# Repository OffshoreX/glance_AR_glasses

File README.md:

# GLANCE: Autofocal Reading Glasses (Board 2)

GLANCE started as AR smart glasses and became a sensing platform for **autofocal reading glasses**. An outward-facing distance sensor measures how far away the object in front of you is. Two inward-facing infrared eye sensors estimate where your eyes are pointing. Together they estimate the distance you are actually looking at, which is the signal a focus-tunable lens would need to adjust itself. The lens itself is out of scope for this project. This repo covers the electronics that do the sensing.

**Status:** PCB design is complete and passes design rule checks. Boards are being ordered for the Hack Club Half Life program. Nothing here has been fabricated or tested yet, so no measured results are claimed.

## How it works

- **Brain:** ESP32-S3-WROOM-1 module (Wi-Fi, BLE and native USB). The antenna end overhangs the board edge.
- **Eye sensing:** one 940 nm IR LED (IR333-A) and one phototransistor (PT334-6B) per eye, on an off-board eye module. Four phototransistor channels are read by an ADS1115 16-bit I2C ADC.
- **Distance sensing:** header for an outward-facing time-of-flight distance sensor module.
- **Power:** USB-C input, MCP73831 Li-ion charger, JST PH battery connector, slide switch for power, AP2112K-3.3 LDO for the 3.3 V rail.
- **Input:** four tactile buttons.

## Images

**Schematic:**

**Before placing and routing:**

**After:**

## Board

- 2-layer FR-4, 37.75 x 65 mm
- Power nets on wider tracks, solid GND pour on both layers
- USB D+ and D- routed by hand as a pair. The remaining signals were autorouted with Freerouting (score 990/1000, 31 vias), then cleaned up by hand
- DRC: zero real errors at submission

## Repo layout

```
hardware/
  board2/                KiCad 10 project (glance-board2.*)
  gerbers/               Gerber and drill files for JLCPCB
  images/                README images
  glance_pcb_bom.csv     Full bill of materials with LCSC part numbers
firmware/                Firmware (ESP32-C3 code from the earlier Board 1 design)
```

Board 1 (the original ESP32-C3 AR design) is kept in the repo for history and is not part of this submission.

## Bill of materials

The full BOM with LCSC part numbers and prices is in [`hardware/glance_pcb_bom.csv`](hardware/glance_pcb_bom.csv). Parts come from LCSC and the bare PCBs from JLCPCB. Several LCSC parts have minimum orders of 5 or 10, so more parts are ordered than the board uses.

Funding note: the Half Life BOM table lists only the items covered by the $30 Tier 1 grant. The remaining parts (ADS1115, charger, LDO, connectors, switches, phototransistors) are bought in the same order and paid for personally. The ESP32-S3 module is also self-funded.

## Firmware

Board 2 firmware has not been written yet. The existing code in `firmware/` targets Board 1's ESP32-C3.

## Next steps

1. Receive the boards and check continuity with a multimeter before powering up.
2. Solder, then bring up power, USB and the ADC.
3. Read the eye sensors and the distance sensor, then estimate gaze distance.

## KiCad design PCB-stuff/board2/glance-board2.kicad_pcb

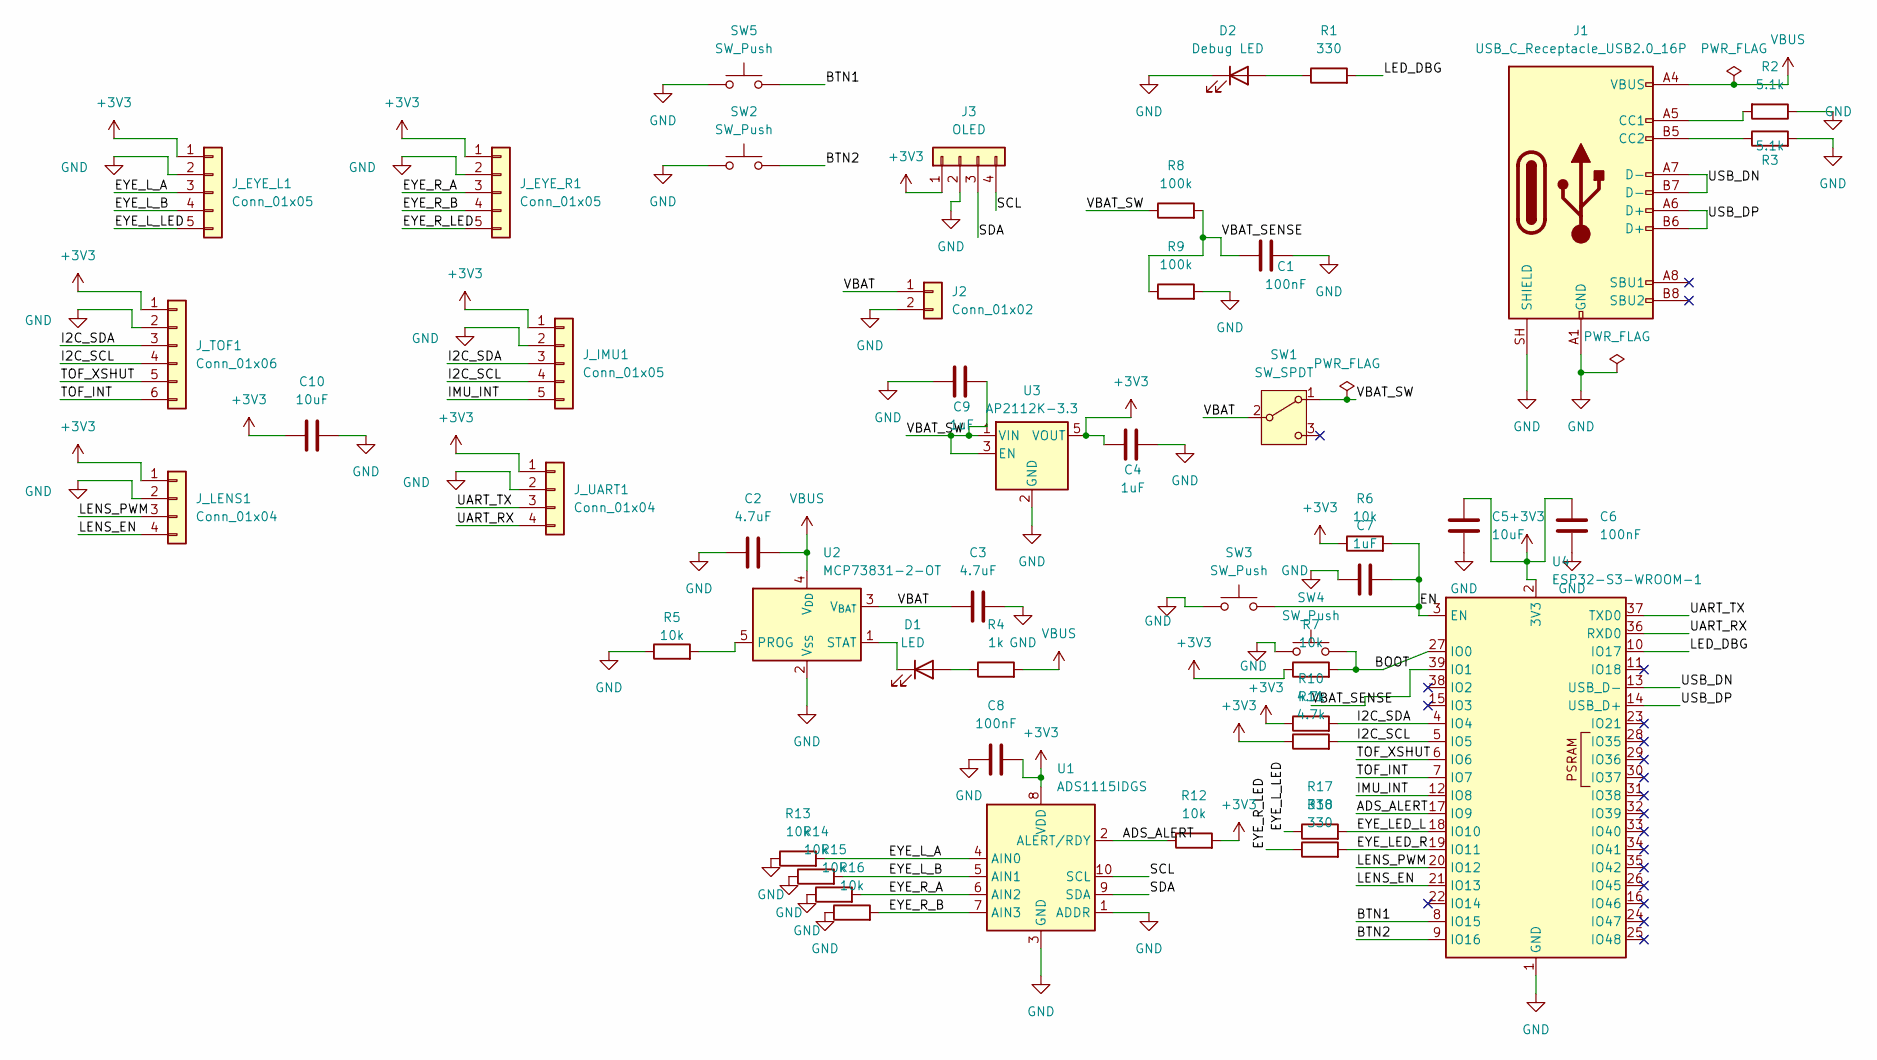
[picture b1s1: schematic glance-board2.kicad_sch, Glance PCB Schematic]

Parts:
C1, C6, C8: 100nF; C_0603_1608Metric
C2, C3: 4.7uF; C_0603_1608Metric
C4, C7, C9: 1uF; C_0603_1608Metric
C5, C10: 10uF; C_0603_1608Metric
D1: LED; LED_0603_1608Metric
D2: Debug LED; LED_0603_1608Metric
J1: USB_C_Receptacle_USB2.0_16P; USB_C_Receptacle_HRO_TYPE-C-31-M-12
J2: Conn_01x02; JST_PH_S2B-PH-K_1x02_P2.00mm_Horizontal
J3: OLED; PinHeader_1x04_P2.54mm_Vertical
J_EYE_L1: Conn_01x05; PinSocket_1x05_P2.54mm_Vertical
J_EYE_R1: Conn_01x05; PinSocket_1x05_P2.54mm_Vertical
J_IMU1: Conn_01x05; PinSocket_1x05_P2.54mm_Vertical
J_LENS1: Conn_01x04; PinSocket_1x04_P2.54mm_Vertical
J_TOF1: Conn_01x06; PinSocket_1x06_P2.54mm_Vertical
J_UART1: Conn_01x04; PinSocket_1x04_P2.54mm_Vertical
R1, R17, R18: 330; R_0603_1608Metric
R2, R3: 5.1k; R_0603_1608Metric
R4: 1k; R_0603_1608Metric
R5, R6, R7, R12, R13, R14, R15, R16: 10k; R_0603_1608Metric
R8, R9: 100k; R_0603_1608Metric
R10, R11: 4.7k; R_0603_1608Metric
SW1: SW_SPDT; SW_SPDT_PCM12
SW2, SW3, SW4, SW5: SW_Push; SW_SPST_B3U-1000P
U1: ADS1115IDGS; TSSOP-10_3x3mm_P0.5mm
U2: MCP73831-2-OT; SOT-23-5
U3: AP2112K-3.3; SOT-23-5
U4: ESP32-S3-WROOM-1

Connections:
+3V3: C4.1, C5.1, C6.1, C8.2, C10.1, J3.1, J_EYE_L1.1, J_EYE_R1.1, J_IMU1.1, J_LENS1.1, J_TOF1.1, J_UART1.1, R6.1, R7.1, R10.1, R11.1, R12.2, U1.8 (VDD), U3.5 (VOUT), U4.2 (3V3)
/ADS_ALERT: R12.1, U1.2 (ALERT/RDY), U4.17 (IO9)
/BOOT: R7.2, SW4.2, U4.27 (IO0)
/BTN1: SW5.2, U4.8 (IO15)
/BTN2: SW2.2, U4.9 (IO16)
/EN: C7.2, R6.2, SW3.2, U4.3 (EN)
/EYE_LED_L: R17.2, U4.18 (IO10)
/EYE_LED_R: R18.2, U4.19 (IO11)
/EYE_L_A: J_EYE_L1.3, R13.2, U1.4 (AIN0)
/EYE_L_B: J_EYE_L1.4, R14.2, U1.5 (AIN1)
/EYE_L_LED: J_EYE_L1.5, R17.1
/EYE_R_A: J_EYE_R1.3, R15.2, U1.6 (AIN2)
/EYE_R_B: J_EYE_R1.4, R16.2, U1.7 (AIN3)
/EYE_R_LED: J_EYE_R1.5, R18.1
/I2C_SCL: J_IMU1.4, J_TOF1.4, R11.2, U4.5 (IO5)
/I2C_SDA: J_IMU1.3, J_TOF1.3, R10.2, U4.4 (IO4)
/IMU_INT: J_IMU1.5, U4.12 (IO8)
/LED_DBG: R1.2, U4.10 (IO17)
/LENS_EN: J_LENS1.4, U4.21 (IO13)
/LENS_PWM: J_LENS1.3, U4.20 (IO12)
/SCL: J3.4, U1.10 (SCL)
/SDA: J3.3, U1.9 (SDA)
/TOF_INT: J_TOF1.6, U4.7 (IO7)
/TOF_XSHUT: J_TOF1.5, U4.6 (IO6)
/UART_RX: J_UART1.4, U4.36 (RXD0)
/UART_TX: J_UART1.3, U4.37 (TXD0)
/USB_DN: J1.A7 (D-), J1.B7 (D-), U4.13 (USB_D-)
/USB_DP: J1.A6 (D+), J1.B6 (D+), U4.14 (USB_D+)
/VBAT: C3.1, J2.1, SW1.2 (B), U2.3 (V_{BAT})
/VBAT_SENSE: C1.2, R8.2, R9.1, U4.39 (IO1)
/VBAT_SW: C9.2, R8.1, SW1.1 (A), U3.1 (VIN), U3.3 (EN)
GND: C1.1, C2.1, C3.2, C4.2, C5.2, C6.2, C7.1, C8.1, C9.1, C10.2, D2.1 (K), J1.A1 (GND), J1.A12 (GND), J1.B1 (GND), J1.B12 (GND), J1.SH (SHIELD), J2.2, J3.2, J_EYE_L1.2, J_EYE_R1.2, J_IMU1.2, J_LENS1.2, J_TOF1.2, J_UART1.2, R2.1, R3.2, R5.1, R9.2, R13.1, R14.1, R15.1, R16.1, SW2.1, SW3.1, SW4.1, SW5.1, U1.1 (ADDR), U1.3 (GND), U2.2 (V_{SS}), U3.2 (GND), U4.1 (GND), U4.40 (GND), U4.41 (GND)
unnamed: D1.2 (A), R4.1
unnamed: D1.1 (K), U2.1 (STAT)
unnamed: D2.2 (A), R1.1
unnamed: J1.A5 (CC1), R2.2
unnamed: J1.B5 (CC2), R3.1
unnamed: R5.2, U2.5 (PROG)
VBUS: C2.2, J1.A4 (VBUS), J1.A9 (VBUS), J1.B4 (VBUS), J1.B9 (VBUS), R4.2, U2.4 (V_{DD})

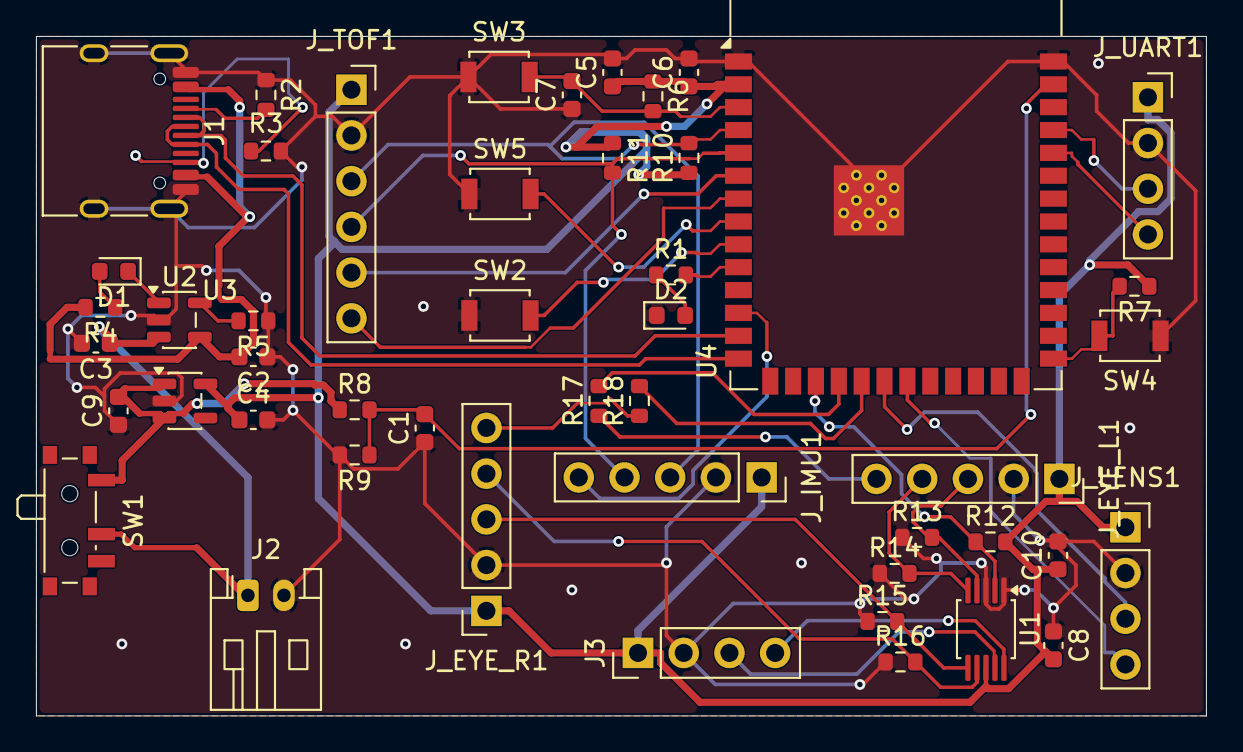
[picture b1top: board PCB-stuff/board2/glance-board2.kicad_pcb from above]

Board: 2 copper layers, 65.0 x 37.8 mm, 48 parts (0 on the bottom side), 39 nets.

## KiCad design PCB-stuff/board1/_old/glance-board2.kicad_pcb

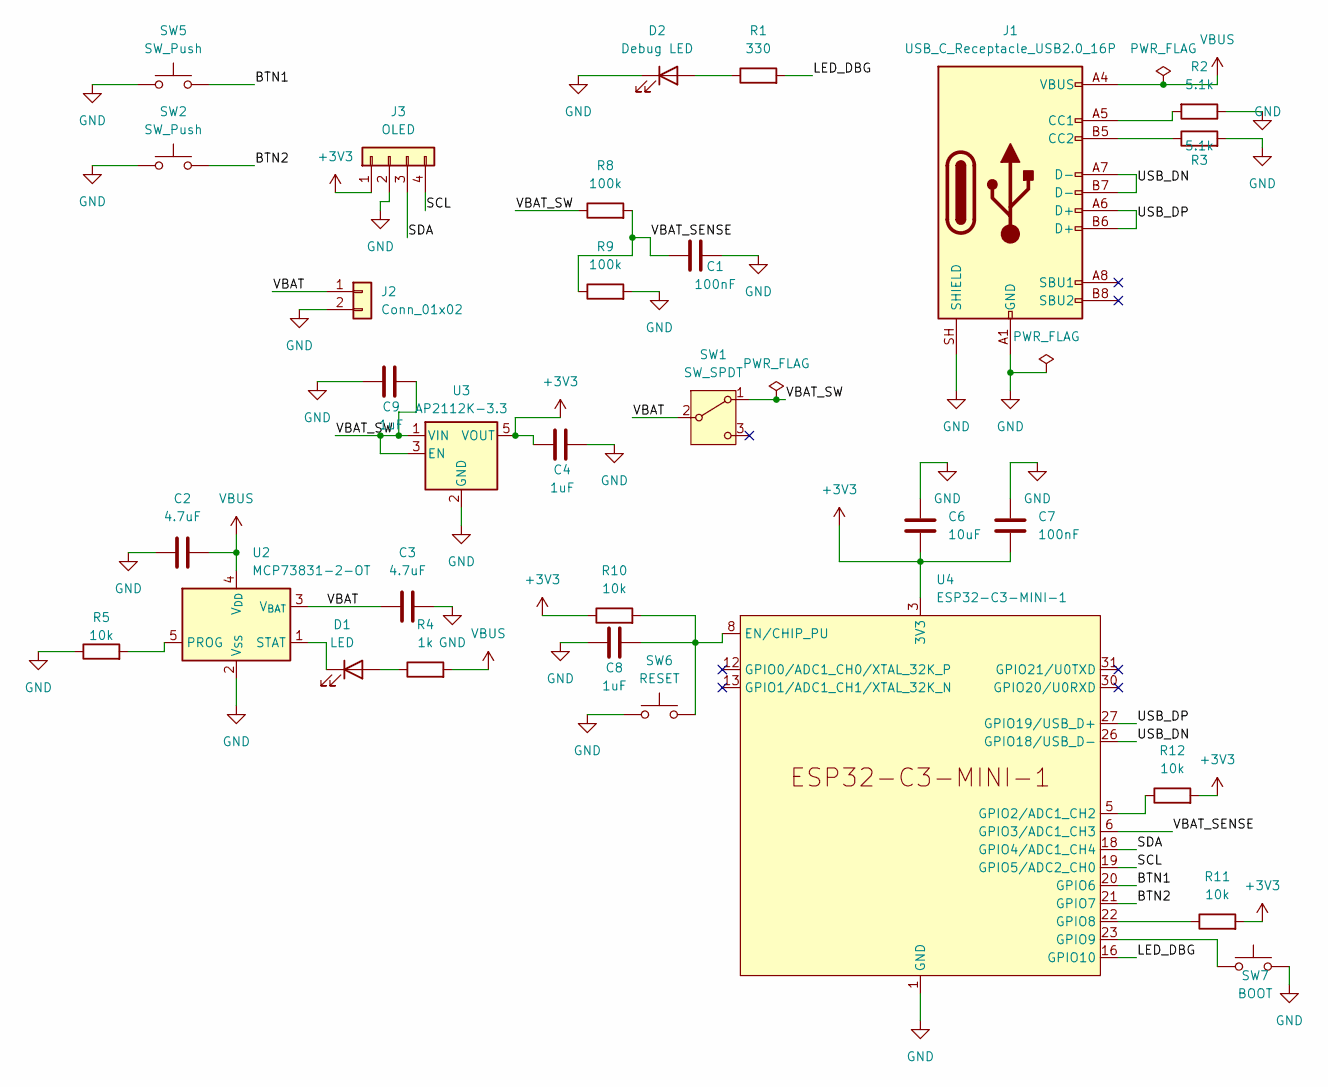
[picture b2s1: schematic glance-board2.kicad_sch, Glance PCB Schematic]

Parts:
C1, C7: 100nF; C_0603_1608Metric
C2, C3: 4.7uF; C_0603_1608Metric
C4, C8, C9: 1uF; C_0603_1608Metric
C6: 10uF; C_0603_1608Metric
D1: LED; LED_0603_1608Metric
D2: Debug LED; LED_0603_1608Metric
J1: USB_C_Receptacle_USB2.0_16P; USB_C_Receptacle_HRO_TYPE-C-31-M-12
J2: Conn_01x02; JST_PH_S2B-PH-K_1x02_P2.00mm_Horizontal
J3: OLED; PinHeader_1x04_P2.54mm_Vertical
R1: 330; R_0603_1608Metric
R2, R3: 5.1k; R_0603_1608Metric
R4: 1k; R_0603_1608Metric
R5, R10, R11, R12: 10k; R_0603_1608Metric
R8, R9: 100k; R_0603_1608Metric
SW1: SW_SPDT; SW_SPDT_PCM12
SW2, SW5: SW_Push; SW_SPST_B3U-1000P
SW6: RESET; SW_SPST_B3U-1000P
SW7: BOOT; SW_SPST_B3U-1000P
U2: MCP73831-2-OT; SOT-23-5
U3: AP2112K-3.3; SOT-23-5
U4: ESP32-C3-MINI-1

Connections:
+3V3: C4.1, C6.2, C7.2, J3.1, R10.1, R11.2, R12.2, U3.5 (VOUT), U4.3 (3V3)
/BTN1: SW5.2, U4.20 (GPIO6)
/BTN2: SW2.2, U4.21 (GPIO7)
/LED_DBG: R1.2, U4.16 (GPIO10)
/SCL: J3.4, U4.19 (GPIO5/ADC2_CH0)
/SDA: J3.3, U4.18 (GPIO4/ADC1_CH4)
/USB_DN: J1.A7 (D-), J1.B7 (D-), U4.26 (GPIO18/USB_D-)
/USB_DP: J1.A6 (D+), J1.B6 (D+), U4.27 (GPIO19/USB_D+)
/VBAT: C3.1, J2.1, SW1.2 (B), U2.3 (V_{BAT})
/VBAT_SENSE: C1.2, R8.2, R9.1, U4.6 (GPIO3/ADC1_CH3)
/VBAT_SW: C9.2, R8.1, SW1.1 (A), U3.1 (VIN), U3.3 (EN)
GND: C1.1, C2.1, C3.2, C4.2, C6.1, C7.1, C8.1, C9.1, D2.1 (K), J1.A1 (GND), J1.A12 (GND), J1.B1 (GND), J1.B12 (GND), J1.SH (SHIELD), J2.2, J3.2, R2.1, R3.2, R5.1, R9.2, SW2.1, SW5.1, SW6.1, SW7.2, U2.2 (V_{SS}), U3.2 (GND), U4.1 (GND), U4.2 (GND), U4.11 (GND), U4.14 (GND), U4.36 (GND), U4.37 (GND), U4.38 (GND), U4.39 (GND), U4.40 (GND), U4.41 (GND), U4.42 (GND), U4.43 (GND), U4.44 (GND), U4.45 (GND), U4.46 (GND), U4.47 (GND), U4.48 (GND), U4.49 (GND), U4.50 (GND), U4.51 (GND), U4.52 (GND), U4.53 (GND)
unnamed: D1.2 (A), R4.1
unnamed: D1.1 (K), U2.1 (STAT)
unnamed: D2.2 (A), R1.1
unnamed: J1.A5 (CC1), R2.2
unnamed: J1.B5 (CC2), R3.1
unnamed: R5.2, U2.5 (PROG)
unnamed: C8.2, R10.2, SW6.2, U4.8 (EN/CHIP_PU)
unnamed: R12.1, U4.5 (GPIO2/ADC1_CH2)
unnamed: R11.1, U4.22 (GPIO8)
unnamed: SW7.1, U4.23 (GPIO9)
VBUS: C2.2, J1.A4 (VBUS), J1.A9 (VBUS), J1.B4 (VBUS), J1.B9 (VBUS), R4.2, U2.4 (V_{DD})

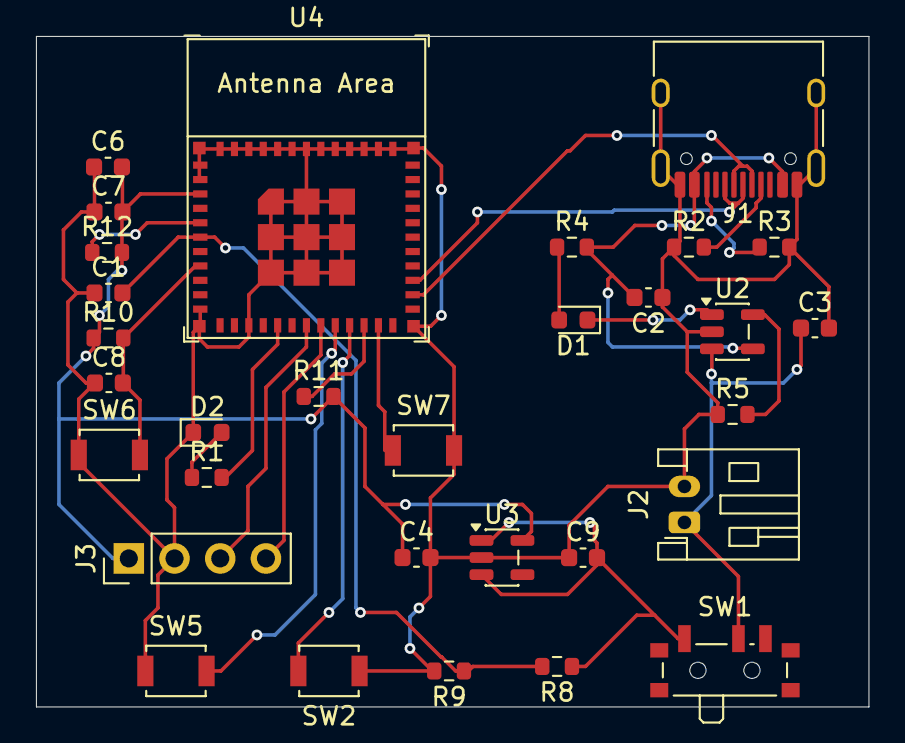
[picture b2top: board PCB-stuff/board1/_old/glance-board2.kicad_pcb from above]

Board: 2 copper layers, 46.2 x 37.2 mm, 31 parts (0 on the bottom side), 23 nets.

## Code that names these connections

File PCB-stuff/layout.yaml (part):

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    members: [J1, R2, R3]

  - name: esp32_support
    description: "EN pull-up, EN cap, SW6 (RESET), SW7 (BOOT), GPIO2 pull-up, GPIO8 pull-up, 3V3 caps."
    members: [R10, C8, SW6, SW7, R12, R11, C6, C7]

  - name: sensing
    description: "Battery divider (R8/R9) and its cap (C1), on /VBAT_SENSE, near U4 GPIO3 (pad 6)."
    members: [R8, R9, C1]

  - name: display
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  - { reference: SW6, group: esp32_support, x: 19.5, y: 15.5, rotation: 0, side: top,
      reason: "Unchanged from file. RESET, pulls EN to GND." }
  - { reference: SW7, group: esp32_support, x: 11.5, y: 18.5, rotation: 0, side: top,
      reason: "Was off-board (abs x=114). Placed in the open pocket directly below U4, close to its own pad 23 (GPIO9)." }
  - { reference: R12, group: esp32_support, x: 15.675, y: 36, rotation: 0, side: top,
      reason: "Unchanged from file. GPIO2 pull-up to +3V3 (strapping pin, per the earlier firmware work's GPIO2 restriction)." }
  - { reference: R11, group: esp32_support, x: 20.675, y: 36, rotation: 0, side: top,
      reason: "Unchanged from file. GPIO8 pull-up to +3V3 (also a strapping pin)." }
  - { reference: C6, group: esp32_support, x: 0.8, y: 23, rotation: 90, side: top, near: { reference: U4, pin: "3V3 (pad 3)" },
      reason: "10uF bulk cap on +3V3. Same left-edge-clearance problem as C8 - see that part's reason. Stacked furthest from U4 since it's the bulk cap, not the fast bypass cap." }
  - { reference: C7, group: esp32_support, x: 0.8, y: 21, rotation: 90, side: top, near: { reference: U4, pin: "3V3 (pad 3)" },
      reason: "100nF bypass cap on +3V3 - stacked closest to U4's pad 3 of the two 3V3 caps, since a small bypass cap wants to be nearest the pin. Same left-edge-clearance caveat as C8." }

  # ---- sensing ----
  - { reference: R8, group: sensing, x: 35.675, y: 36, rotation: 0, side: top, near: { reference: U4, pin: "GPIO3/ADC1_CH3 (pad 6)" },
      reason: "Unchanged from file. Top half of the battery divider (/VBAT_SW to /VBAT_SENSE)." }
  - { reference: R9, group: sensing, x: 30.675, y: 36, rotation: 0, side: top, near: { reference: U4, pin: "GPIO3/ADC1_CH3 (pad 6)" },
      reason: "Unchanged from file. Bottom half of the divider (/VBAT_SENSE to GND)." }
  - { reference: C1, group: sensing, x: 0.8, y: 17, rotation: 90, side: top, near: { reference: U4, pin: "GPIO3/ADC1_CH3 (pad 6)" },
      reason: "Filter cap on /VBAT_SENSE to GND, same net as U4 pad 6 (GPIO3). Same left-edge-clearance problem as C8/C6/C7 - pad 6 is also on U4's left castellated edge. Placed closest to the actual pad of the four left-edge caps." }

  # ---- display ----
  - { reference: J3, group: display, x: 13, y: 22.5, rotation: 0, side: top, near: { reference: U4, pin: "SDA/SCL (pads 18/19)" },
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
  # ---- user_io ----
  - { reference: SW2, group: user_io, x: 6.5, y: 18.5, rotation: 0, side: top,
      reason: "Was off-board (abs x=114.3). Placed in the open pocket below U4, close to its own pad 21 (GPIO7/BTN2), next to SW7." }
  - { reference: SW5, group: user_io, x: 27, y: 15.5, rotation: 0, side: top,
      reason: "Unchanged from file. BTN1." }
  - { reference: D2, group: user_io, x: 39, y: 15, rotation: 0, side: top,
      reason: "Unchanged from file. Debug LED, cathode to GND." }
  - { reference: R1, group: user_io, x: 34.675, y: 26, rotation: 0, side: top,
      reason: "Unchanged from file. D2's series resistor to U4 pad 16 (GPIO10/LED_DBG); no touching requirement for resistors." }

# Coverage check (printed, not asserted as correct - see note below)
# Footprints in glance-pcb.kicad_pcb: 30
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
